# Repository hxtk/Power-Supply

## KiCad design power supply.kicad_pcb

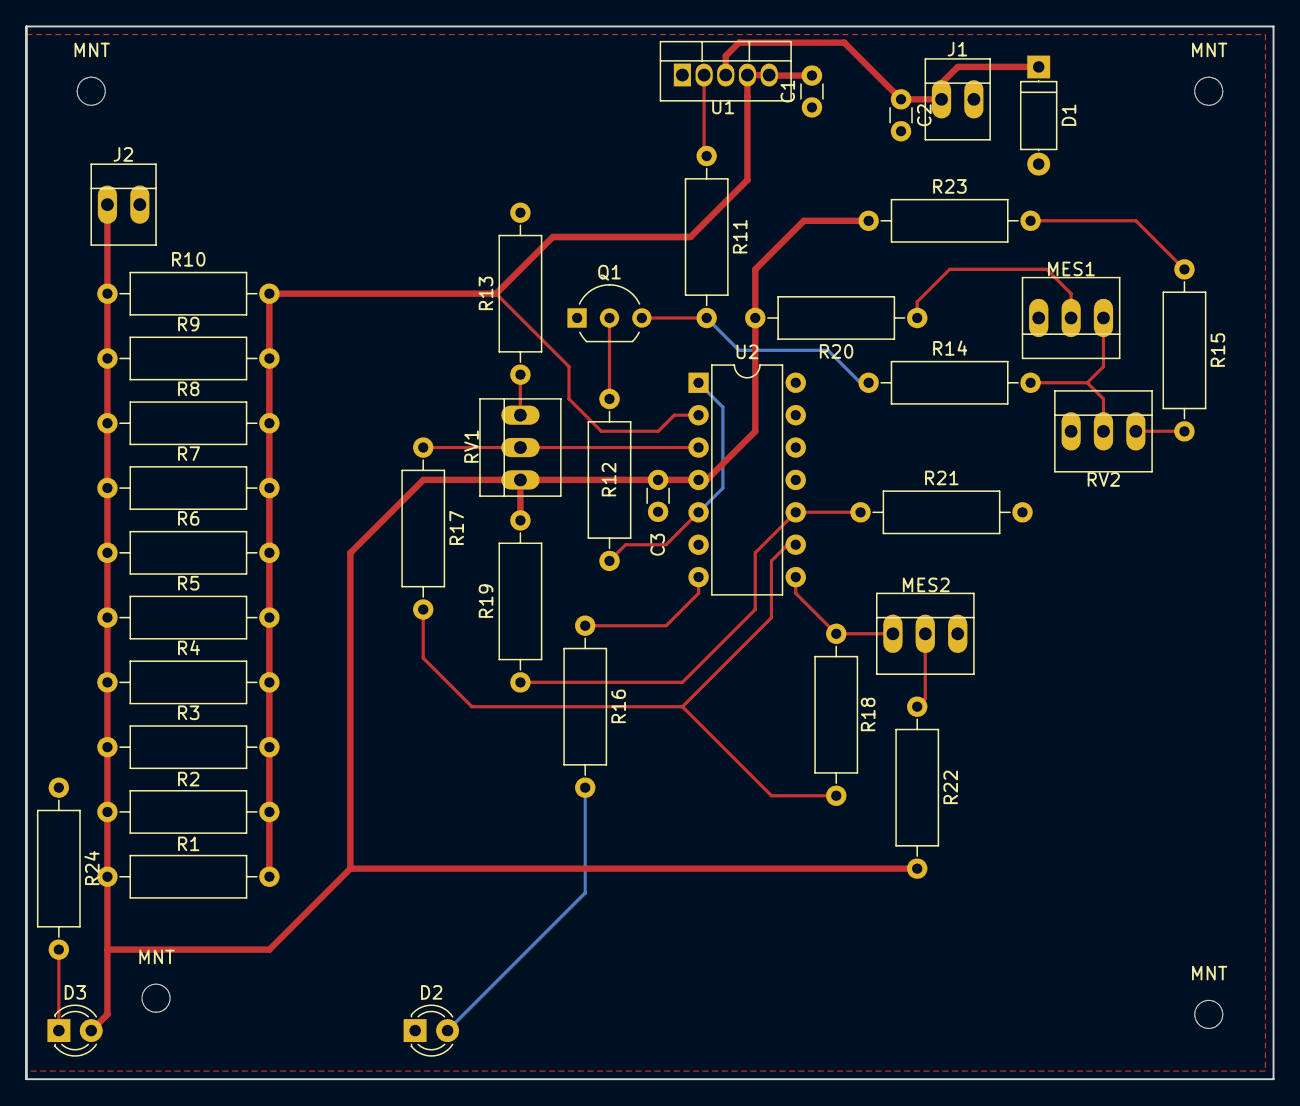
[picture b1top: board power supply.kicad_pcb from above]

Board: 2 copper layers, 97.8 x 82.5 mm, 43 parts (0 on the bottom side), 21 nets.

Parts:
C1, C2, C3: C; C_Disc_D3.0mm_W1.6mm_P2.50mm
D1: D; D_A-405_P7.62mm_Horizontal
D2, D3: LED; LED_D3.0mm
J1, J2: CONN_01X02_FEMALE; PINHEAD1-2
MES1, MES2: 3B002; PINHEAD1-3
MNT: MountingHole_2.2mm_M2
MNT#2, MNT#3, MNT#4: MountingHole_2.2mm_M2
Q1: PN2222A; TO-92_Inline_Wide
R1, R2, R3, R4, R5, R6, R7, R8, R9, R10, R11, R12, R13, R14, R15, R16, R17, R18, R19, R20, R21, R22, R23, R24: R; R_Axial_DIN0309_L9.0mm_D3.2mm_P12.70mm_Horizontal
RV1, RV2: POT; PINHEAD1-3
U1: LT3080; TO-220-5_Pentawatt_Multiwatt-5_Vertical
U2: LM324; DIP-14_W7.62mm

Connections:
+12V: C3.1, D3.2, J2.1, R1.1, R2.1, R3.1, R4.1, R5.1, R6.1, R7.1, R8.1, R9.1, R10.1, R19.2, R20.2, R22.2, R23.1, RV1.1, U2.4
/Isense: C1.2, R1.2, R2.2, R3.2, R4.2, R5.2, R6.2, R7.2, R8.2, R9.2, R10.2, U1.4, U1.5, U2.2
/Iset: R17.1, RV1.2, U2.3
/OUT: C2.1, D1.1, J1.1, U1.3
/Vset: MES1.1, R14.2, RV2.2
GND: C1.1, C2.2, C3.2, D1.2, D2.1, J1.2, J2.2, MES1.3, MES2.3, Q1.1, R13.2, R21.2, R24.1, RV2.1, U2.6, U2.11
unnamed: D2.2, R16.2
unnamed: D3.1, R24.2
unnamed: MES1.2, R20.1
unnamed: MES2.1, R18.2, U2.8
unnamed: MES2.2, R22.1
unnamed: Q1.2, R12.1
unnamed: Q1.3, R11.2, R14.1
unnamed: R11.1, U1.2
unnamed: R12.2, U2.1, U2.5
unnamed: R13.1, RV1.3
unnamed: R15.1, R23.2
unnamed: R15.2, RV2.3
unnamed: R16.1, U2.7
unnamed: R17.2, R18.1, U2.9
unnamed: R19.1, R21.1, U2.10

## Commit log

2017-09-25 Add LT3080 and voltmeter to libraries
2017-09-25 Circuit design
2017-09-25 Route PCB
2017-09-25 Heat dissipation calculations
2017-09-25 remove acid trap
2017-09-25 Gerber files
2017-09-25 Thicker traces for high-power rails
2017-09-25 Add kicad project file
2017-09-27 PDF of schematic
2017-09-28 Fix pin orientation on voltmeters
